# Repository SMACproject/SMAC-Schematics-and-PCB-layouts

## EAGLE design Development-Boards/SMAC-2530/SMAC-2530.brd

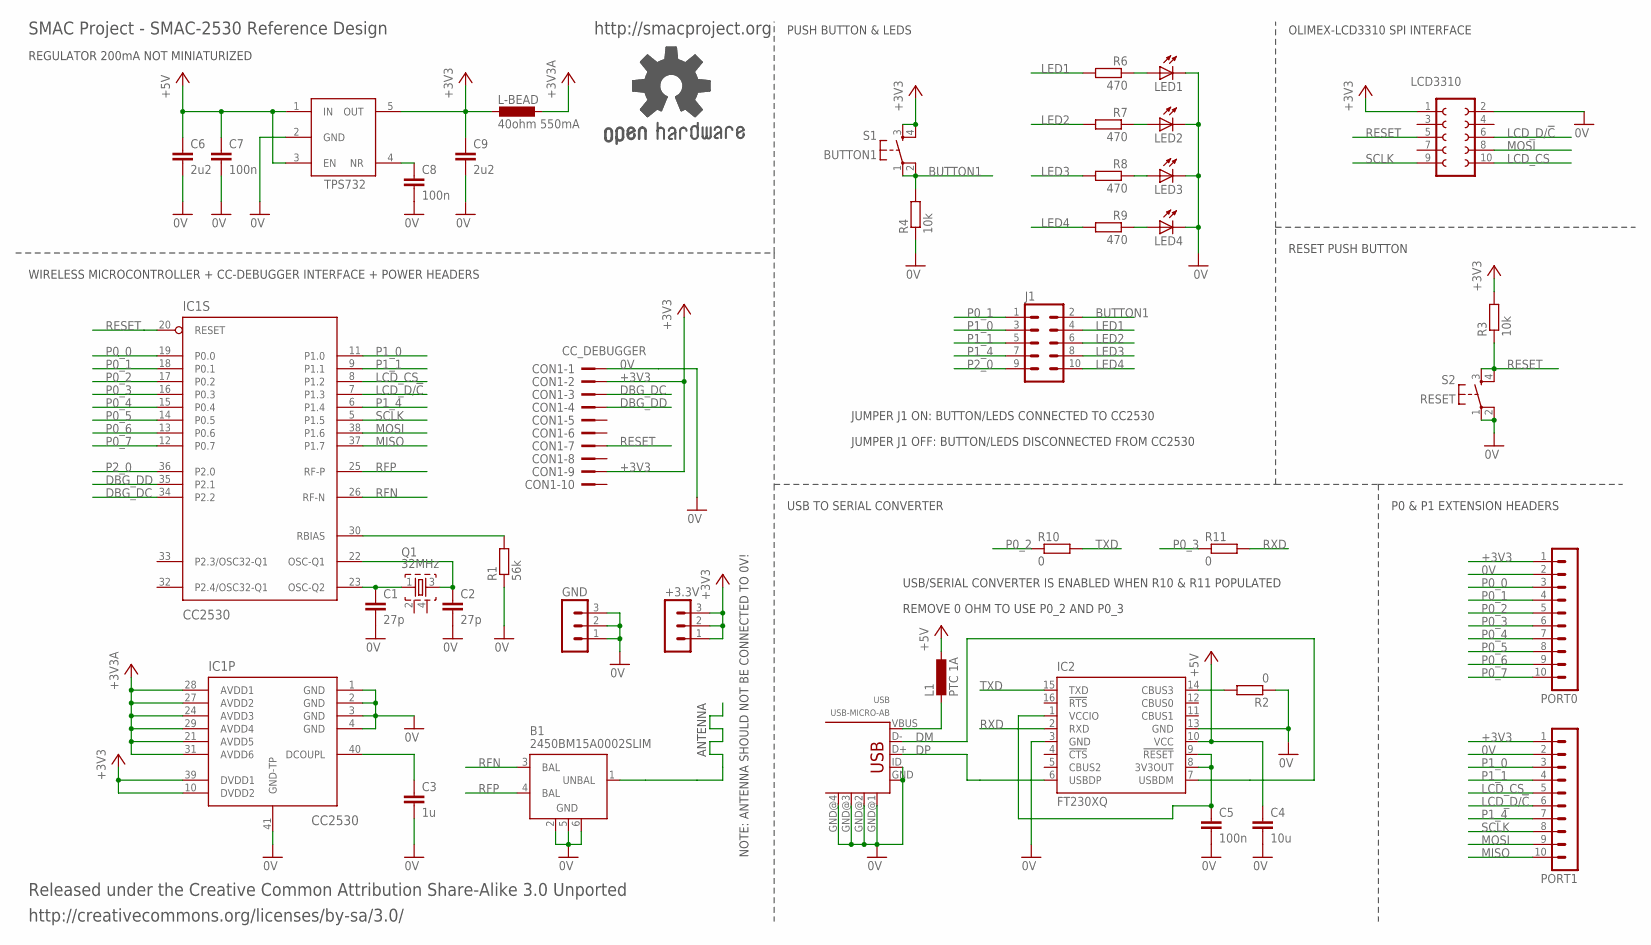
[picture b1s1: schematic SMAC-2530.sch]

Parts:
+3.3V: MA03-1
B1: 2450BM15A0002SLIM; 2450BM15A0002-SLIM
C1, C2: 27p; C0603K
C3: 1u; C0603K
C4: 10u; C0603K
C5, C7, C8: 100n; C0603K
C6, C9: 2u2; C0603K
CON1: CC_DEBUGGER; PAK100/2500-10
GND: MA03-1
GOLD_ORB_SM1: OSHWLOGO_GOLD_ORB_SM; OSHW2
IC1: CC2530; QFN50P600X600X100-41N
IC2: FT230XQ; QFN16
IC3: TPS732XX; SOT23
J1: MA05-2
L1: PTC 1A; L0603K
L-BEAD: 40ohm 550mA; L0603K
LCD3310: FE05-2
LED1, LED2, LED3, LED4: LEDCHIP-LED0805; CHIP-LED0805
PORT0, PORT1: MA10-1
Q1: 32MHz; FA-128
R1: 56k; R0603K
R2, R10, R11: 0; R0603K
R3, R4: 10k; R0603K
R6, R7, R8, R9: 470; R0603K
S1: BUTTON1; ALCOSWITCH-SMD
S2: RESET; ALCOSWITCH-SMD
USB: USB-MICRO-AB; USB-UAB-S1

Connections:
0V: B1.1 (UNBAL), B1.2 (GND), B1.5 (GND), B1.6 (GND), C1.2, C2.2, C3.2, C4.2, C5.2, C6.2, C7.2, C8.2, C9.2, CON1.1, GND.1, GND.2, GND.3, IC1.1 (GND), IC1.2 (GND), IC1.3 (GND), IC1.4 (GND), IC1.41 (GND-TP), IC2.3 (GND), IC2.13 (GND), IC3.2 (GND), LCD3310.2, LED1.C, LED2.C, LED3.C, LED4.C, PORT0.2, PORT1.2, R1.1, R2.1, R4.1, S2.1, S2.2 (P1), USB.GND, USB.GND@1 (GND), USB.GND@2 (GND), USB.GND@3 (GND), USB.GND@4 (GND), USB.ID
+3V3: +3.3V.1, +3.3V.2, +3.3V.3, C9.1, CON1.2, CON1.9, IC1.10 (DVDD2), IC1.39 (DVDD1), IC3.5 (OUT), L-BEAD.1, LCD3310.1, PORT0.1, PORT1.1, R3.2, S1.3 (S), S1.4 (S1)
+3V3A: IC1.21 (AVDD5), IC1.24 (AVDD3), IC1.27 (AVDD2), IC1.28 (AVDD1), IC1.29 (AVDD4), IC1.31 (AVDD6), L-BEAD.2
+5V: C4.1, C6.1, C7.1, IC2.10 (VCC), IC3.1 (IN), IC3.3 (EN), L1.1
BUTTON1: J1.2, R4.2, S1.1, S1.2 (P1)
DBG_DC: CON1.3, IC1.34 (P2.2)
DBG_DD: CON1.4, IC1.35 (P2.1)
DM: IC2.7 (USBDM), USB.D-
DP: IC2.6 (USBDP), USB.D+
LCD_CS: IC1.8 (P1.2), LCD3310.10, PORT1.5
LCD_D/!C: IC1.7 (P1.3), LCD3310.6, PORT1.6
LED1: J1.4, R6.2
LED2: J1.6, R7.2
LED3: J1.8, R8.2
LED4: J1.10, R9.2
MISO: IC1.37 (P1.7), PORT1.10
MOSI: IC1.38 (P1.6), LCD3310.8, PORT1.9
unnamed: C3.1, IC1.40 (DCOUPL)
unnamed: L1.2, USB.VBUS
unnamed: C2.1, IC1.22 (OSC-Q1), Q1.3
unnamed: C1.1, IC1.23 (OSC-Q2), Q1.1
unnamed: IC1.30 (RBIAS), R1.2
unnamed: IC2.14 (CBUS3), R2.2
unnamed: C8.1, IC3.4 (NR)
unnamed: LED1.A, R6.1
unnamed: LED2.A, R7.1
unnamed: LED3.A, R8.1
unnamed: LED4.A, R9.1
P0_0: IC1.19 (P0.0), PORT0.3
P0_1: IC1.18 (P0.1), J1.1, PORT0.4
P0_2: IC1.17 (P0.2), PORT0.5, R10.1
P0_3: IC1.16 (P0.3), PORT0.6, R11.1
P0_4: IC1.15 (P0.4), PORT0.7
P0_5: IC1.14 (P0.5), PORT0.8
P0_6: IC1.13 (P0.6), PORT0.9
P0_7: IC1.12 (P0.7), PORT0.10
P1_0: IC1.11 (P1.0), J1.3, PORT1.3
P1_1: IC1.9 (P1.1), J1.5, PORT1.4
P1_4: IC1.6 (P1.4), J1.7, PORT1.7
P2_0: IC1.36 (P2.0), J1.9
RESET: CON1.7, IC1.20 (RESET), LCD3310.5, R3.1, S2.3 (S), S2.4 (S1)
RFN: B1.3 (BAL), IC1.26 (RF-N)
RFP: B1.4 (BAL), IC1.25 (RF-P)
RXD: IC2.2 (RXD), R11.2
SCLK: IC1.5 (P1.5), LCD3310.9, PORT1.8
TXD: IC2.15 (TXD), R10.2
VIO: C5.1, IC2.1 (VCCIO), IC2.8 (3V3OUT), IC2.9 (!RESET)

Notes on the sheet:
REGULATOR 200mA NOT MINIATURIZED
ANTENNA
WIRELESS MICROCONTROLLER + CC-DEBUGGER INTERFACE + POWER HEADERS
USB TO SERIAL CONVERTER
USB/SERIAL CONVERTER IS ENABLED WHEN R10 & R11 POPULATED
REMOVE 0 OHM TO USE P0_2 AND P0_3
P0 & P1 EXTENSION HEADERS
RESET PUSH BUTTON
OLIMEX-LCD3310 SPI INTERFACE
PUSH BUTTON & LEDS
JUMPER J1 ON: BUTTON/LEDS CONNECTED TO CC2530
JUMPER J1 OFF: BUTTON/LEDS DISCONNECTED FROM CC2530
Released under the Creative Common Attribution Share-Alike 3.0 Unported
http://creativecommons.org/licenses/by-sa/3.0/
SMAC Project - SMAC-2530 Reference Design
http://smacproject.org
NOTE: ANTENNA SHOULD NOT BE CONNECTED TO 0V!

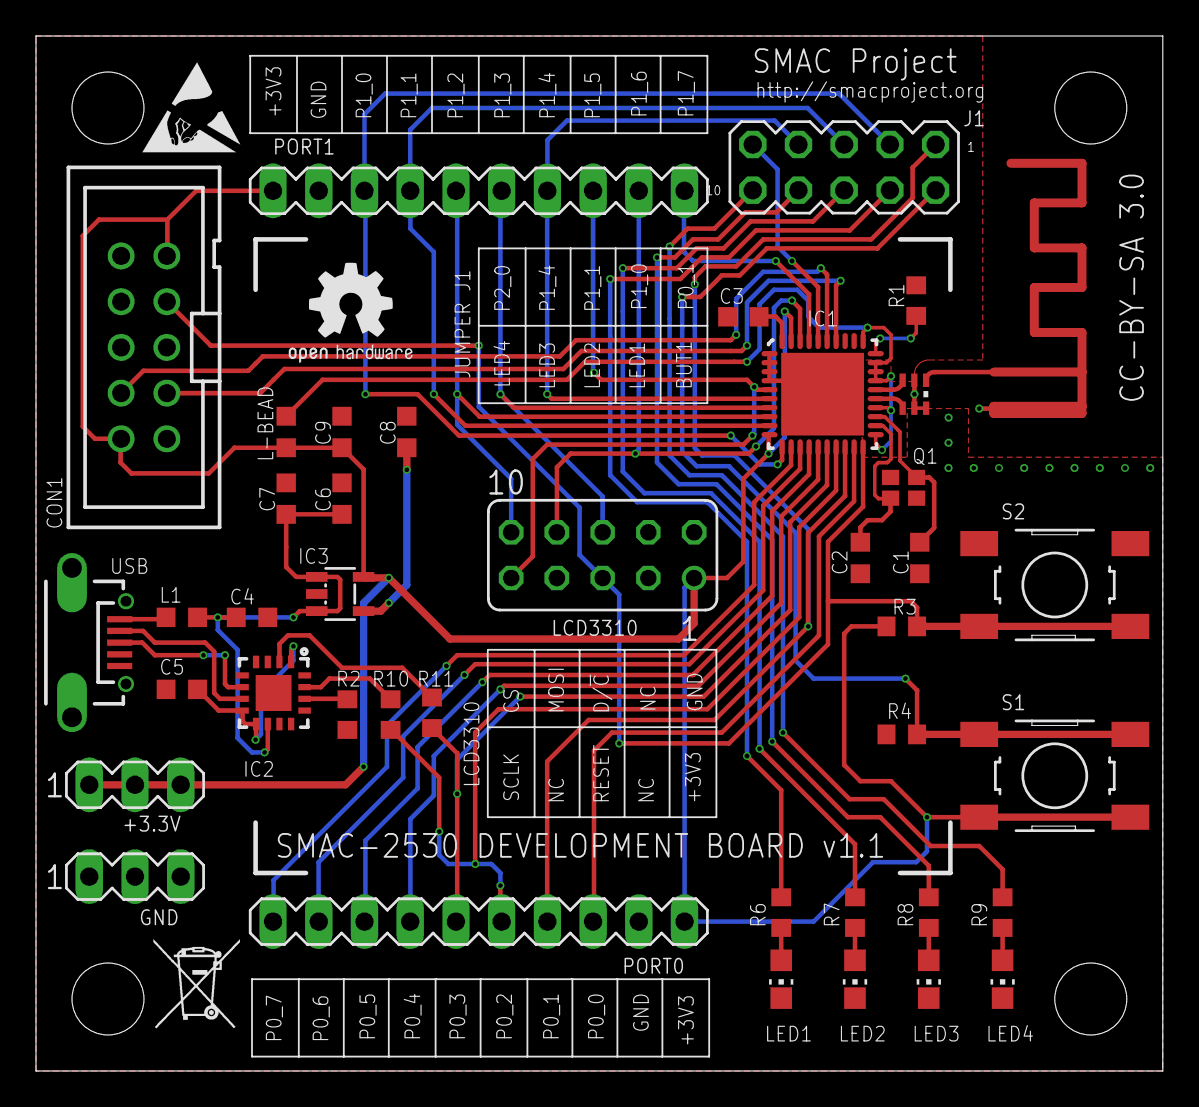
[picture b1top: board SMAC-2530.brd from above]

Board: 4 copper layers, 62.6 x 57.5 mm, 41 parts (0 on the bottom side), 47 nets.

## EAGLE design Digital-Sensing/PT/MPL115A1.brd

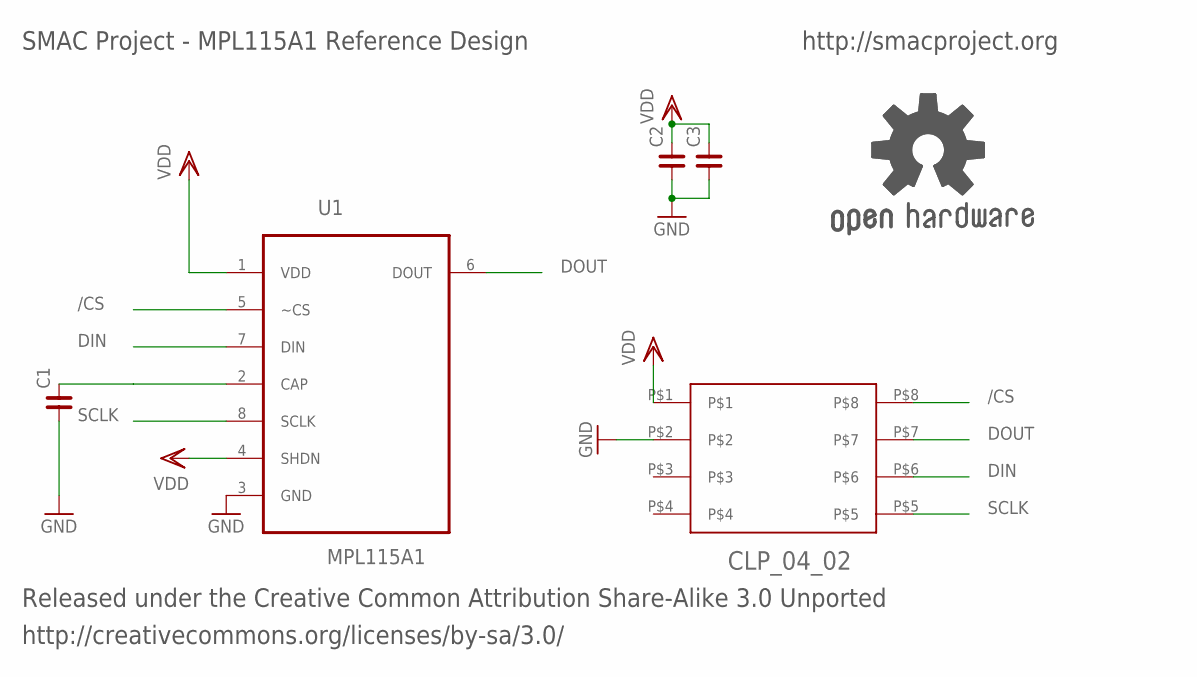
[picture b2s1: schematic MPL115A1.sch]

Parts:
C1, C2, C3: C_0402; C0402
GOLD_ORB_SM2: OSHWLOGO_REF_SM; OSHW2REF
U1: MPL115A1; LGA8R125P0X4_500X300X120
U$1: CLP_04_02; CLP-104

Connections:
/CS: U1.5 (~CS), U$1.P$8
DIN: U1.7 (DIN), U$1.P$6
DOUT: U1.6 (DOUT), U$1.P$7
GND: C1.1, C2.1, C3.1, U1.3 (GND), U$1.P$2
unnamed: C1.2, U1.2 (CAP)
SCLK: U1.8 (SCLK), U$1.P$5
VDD: C2.2, C3.2, U1.1 (VDD), U1.4 (SHDN), U$1.P$1

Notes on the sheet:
Released under the Creative Common Attribution Share-Alike 3.0 Unported
http://creativecommons.org/licenses/by-sa/3.0/
SMAC Project - MPL115A1 Reference Design
http://smacproject.org

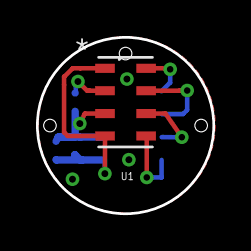
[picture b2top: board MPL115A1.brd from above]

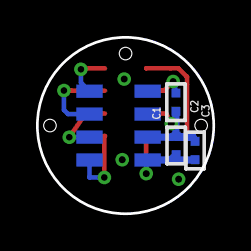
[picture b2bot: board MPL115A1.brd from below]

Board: 2 copper layers, 9.8 x 9.8 mm, 6 parts (4 on the bottom side), 7 nets.

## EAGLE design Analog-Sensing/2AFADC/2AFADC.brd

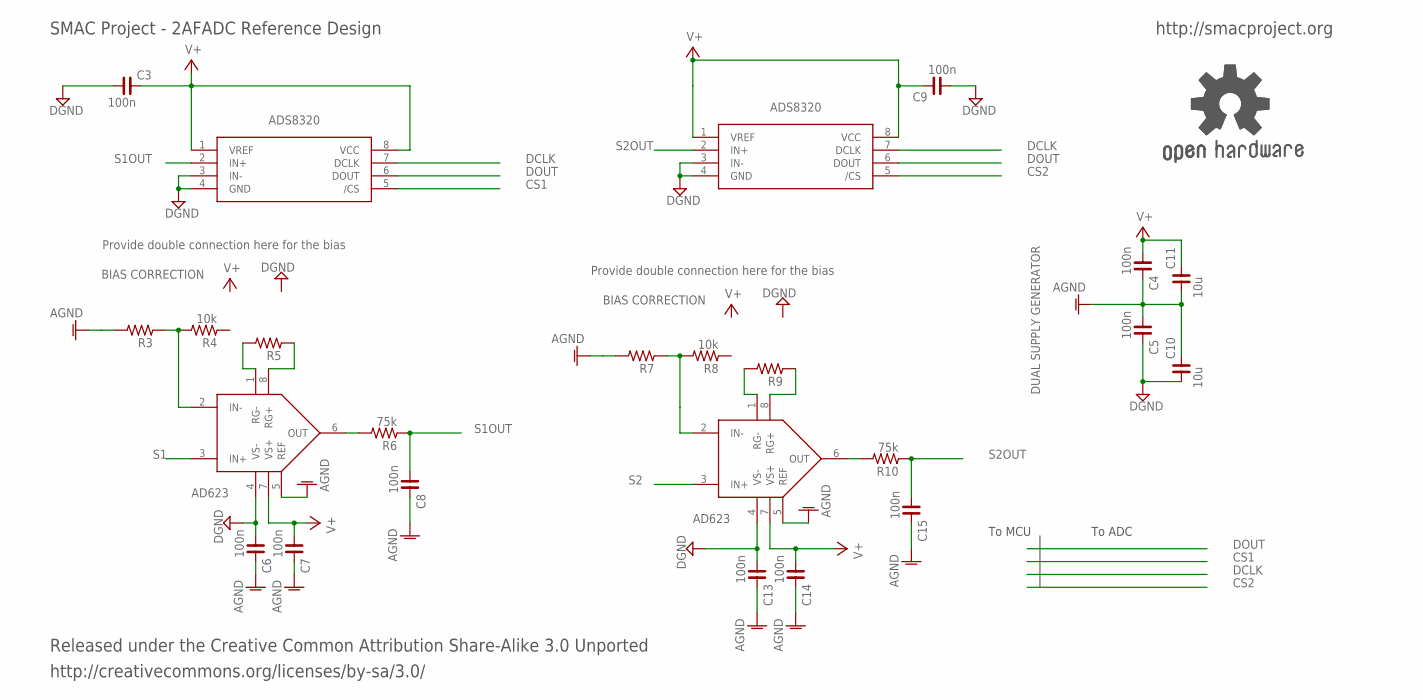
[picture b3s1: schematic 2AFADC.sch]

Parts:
C3, C4, C5, C6, C7, C8, C9, C13, C14, C15: 100n; C0402
C10, C11: 10u; C0402
GOLD_ORB_SM1: OSHWLOGO_REF_SM; OSHW2REF
R3, R5, R7, R9: R_0402; R0402
R4, R8: 10k; R0402
R6, R10: 75k; R0402
U$2, U$3: AD623MSOP8; MSOP8
U$5, U$6: ADS8320MSOP8; MSOP8

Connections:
AGND: C4.2, C5.1, C6.2, C7.2, C8.2, C10.2, C11.1, C13.2, C14.2, C15.2, R3.2, R7.2, U$2.5 (REF), U$3.5 (REF)
CS1: U$5.5 (/CS)
CS2: U$6.5 (/CS)
DCLK: U$5.7 (DCLK), U$6.7 (DCLK)
DGND: C3.1, C5.2, C6.1, C9.1, C10.1, C13.1, U$2.4 (VS-), U$3.4 (VS-), U$5.3 (IN-), U$5.4 (GND), U$6.3 (IN-), U$6.4 (GND)
DOUT: U$5.6 (DOUT), U$6.6 (DOUT)
unnamed: R3.1, R4.2, U$3.2 (IN-)
unnamed: R5.2, U$3.1 (RG-)
unnamed: R5.1, U$3.8 (RG+)
unnamed: R6.2, U$3.6 (OUT)
unnamed: R9.2, U$2.1 (RG-)
unnamed: R9.1, U$2.8 (RG+)
unnamed: R10.2, U$2.6 (OUT)
unnamed: R7.1, R8.2, U$2.2 (IN-)
S1: U$3.3 (IN+)
S1OUT: C8.1, R6.1, U$5.2 (IN+)
S2: U$2.3 (IN+)
S2OUT: C15.1, R10.1, U$6.2 (IN+)
V+: C3.2, C4.1, C7.1, C9.2, C11.2, C14.1, U$2.7 (VS+), U$3.7 (VS+), U$5.1 (VREF), U$5.8 (VCC), U$6.1 (VREF), U$6.8 (VCC)

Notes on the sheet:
BIAS CORRECTION
DUAL SUPPLY GENERATOR
Provide double connection here for the bias
To MCU
To ADC
Released under the Creative Common Attribution Share-Alike 3.0 Unported
http://creativecommons.org/licenses/by-sa/3.0/
SMAC Project - 2AFADC Reference Design
http://smacproject.org

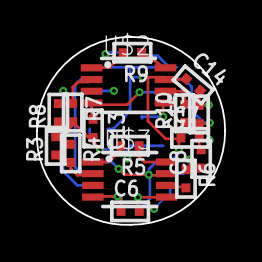
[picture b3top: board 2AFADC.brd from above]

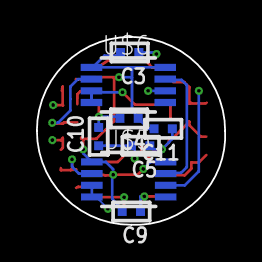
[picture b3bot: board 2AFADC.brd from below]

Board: 4 copper layers, 10.5 x 10.4 mm, 25 parts (8 on the bottom side), 15 nets.

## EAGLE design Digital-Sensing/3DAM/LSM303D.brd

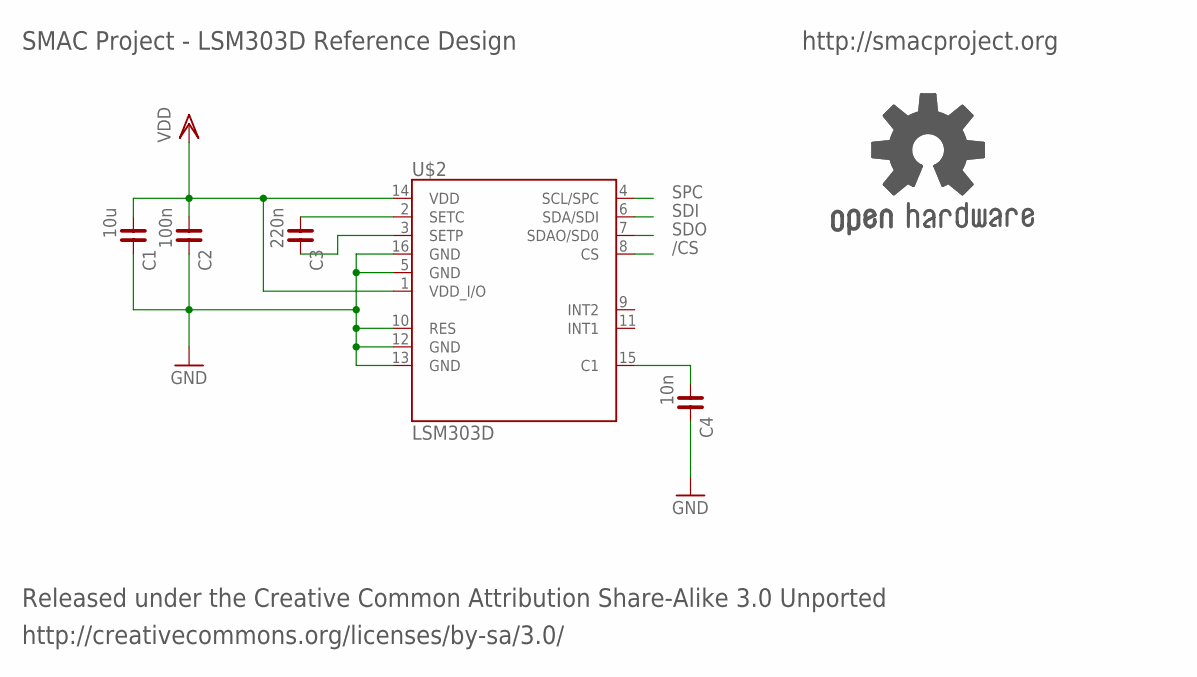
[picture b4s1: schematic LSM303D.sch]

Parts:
C1: 10u; C0402
C2: 100n; C0402
C3: 220n; C0402
C4: 10n; C0402
GOLD_ORB_SM2: OSHWLOGO_REF_SM; OSHW2REF
U$2: LSM303D; LGA16-3MM

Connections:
/CS: U$2.8 (CS)
GND: C1.2, C2.2, C4.2, U$2.5 (GND), U$2.10 (RES), U$2.12 (GND), U$2.13 (GND), U$2.16 (GND)
unnamed: C3.1, U$2.2 (SETC)
unnamed: C4.1, U$2.15 (C1)
unnamed: C3.2, U$2.3 (SETP)
SDI: U$2.6 (SDA/SDI)
SDO: U$2.7 (SDAO/SD0)
SPC: U$2.4 (SCL/SPC)
VDD: C1.1, C2.1, U$2.1 (VDD_I/O), U$2.14 (VDD)

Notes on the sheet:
Released under the Creative Common Attribution Share-Alike 3.0 Unported
http://creativecommons.org/licenses/by-sa/3.0/
SMAC Project - LSM303D Reference Design
http://smacproject.org

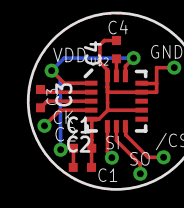
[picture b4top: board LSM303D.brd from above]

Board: 2 copper layers, 6 parts (0 on the bottom side), 5 nets.

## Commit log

2014-10-07 Added AD7689 module reference design
2014-10-07 Added BH67172NUX reference design
2014-10-07 minor update OSHW logo
2014-10-07 Added BH67172NUX-FPC reference design
2014-10-08 Added Power Management reference design
2014-10-08 Added A3901 reference design
2014-10-08 Added L3GD20 reference design
2014-10-08 Added LIS3MDL reference design
2014-10-08 Added LIS331DLH reference design
2014-10-08 Added LSM9DS0 reference design
2014-10-08 minor modification on OSHW logo; added LSM330DLC reference design
2014-10-08 Added LED module reference design
2014-10-08 Added CC2530 reference design
2014-10-08 Adding PDF generated schematic for modules
2014-10-08 Added SMAC-2530 reference design
2014-10-08 Added CC2530EV reference design; added PDF schematics
2014-10-08 Added list of modules
2014-10-09 updating readme
2014-10-09 restructuring folders
2014-10-09 updating read me to include quick links to module descriptions
2014-10-09 updating development board links
2014-10-09 Added Pressure/Temperature and analog front end reference designs
2014-10-09 Adding CC2530EV image
2014-10-09 Updating CC2530EV readme
2014-10-09 restructuring CC2530EV folder
2014-10-09 Added SMAC-2530 read me
2014-10-10 resizing pictures
2014-10-10 added CC2350 master module picture and readme
2014-10-10 added AD7689 reference design
2014-12-11 SMAC-2530 release v1.1, better antenna grounding, removed R0 jumper

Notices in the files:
Development-Boards/SMAC-2530/SMAC-2530.brd:
CC-BY-SA 3.0
parts and their libraries:
rc-master-smd: Copyright (C) 2007, Bob Starr
SparkFun-Sensors: Licensing: Creative Commons ShareAlike 4.0 International - https://creativecommons.org/licenses/by-sa/4.0
